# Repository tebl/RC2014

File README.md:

# RC2014

I've been spending a lot of time lately working on extensions to the excellent RC2014 machine, check out the official web page at [http://rc2014.co.uk](http://rc2014.co.uk) if you're not familiar with it. Short story; it's a Z80-based homecomputer that you can build yourself using a soldering iron, lots of time and severely burned fingers. A lot of fun indeed!

I've been documenting the build process of the various components on my blog at [https://hvetebolle.blogspot.no/p/rc2014.html](https://hvetebolle.blogspot.no/p/rc2014.html), but take note that it's in my native language of Norwegian so it might not register as readable for most people.

## Modules

I'll be making a subfolder for each of the modules I've been working on, most of the files will be in KiCad format so you'll need this open source application installed if you intend to work with the schematics. For the most part I will include the necessary Gerber files (for PCB production) in each modules export folder, the schematic in PDF-format will also probably be included - also, in the export folder.

* [RC2014 IDE ATA adapter](https://github.com/tebl/RC2014/tree/master/RC2014%20IDE)
* [RC2014 Pageable RAM](https://github.com/tebl/RC2014/tree/master/RC2014%20RAM)
* [RC2014 Tandy Sound Card](https://github.com/tebl/RC2014/tree/master/RC2014%20Tandy%20Sound%20Card)

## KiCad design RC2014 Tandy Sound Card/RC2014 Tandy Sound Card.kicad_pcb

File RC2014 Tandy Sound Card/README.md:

# RC2014 Tandy Sound Card

This is a sound card for the RC2014 that I've been tinkering with, it's based on the SN76489N chip so it should be something akin to the original Tandy Sound Card. Not that I actually had one of those mind you, I was lucky enough to have a computer in the early 90s and that was years before I managed to get a hold of my first used sound card (Creative Soundblaster 8-bit). Anyways, I digress...

# Schematic
The supplied KiCad files should be sufficient as both a schematic and as a starting point for ordering PCBs (basically you could just zip the contents of the export folder and upload that on a fabrication site), the schematic is also available in [PDF-format](https://github.com/tebl/RC2014/raw/master/RC2014%20Tandy%20Sound%20Card/export/RC2014%20Tandy%20Sound%20Card.pdf) so that you can refer to it while troubleshooting bad solder joints.

# BOM
This is the part list as it stands now, having not yet received nor assembled the first version of this card so some changes will probably happen. Note that since this includes a lot of circuitry dealing with amplifying the signal, some parts of this may be left out if they are not needed. Jack socket may be omitted if you only want to attach a simple speaker to it using the one of the two speaker outputs J2 and J3 (with amplification). Crystal may be omitted, instead you can use the system clock with the clock divider to get this below SN76489AN max frequency (4 Mhz) - with a stock RC2014 you would atleast need to set J6 to divide it in half.

| Reference | Item                                  | Count |
| --------- | ------------------------------------- | ----- |
| PCB       | Fabricate yourself using Gerber files |     1 |
| U1        | 74HCT138 DIP                          |     1 |
| U2        | 74HCT245 DIP                          |     1 |
| U3        | SN76489AN DIP                         |     1 |
| U4        | TDA7056A SIP (mono amplifier)         |     1 |
| U5        | 74HCT74 DIP                           |     1 |
| RV1 - RV2 | Adjustable resistor, 10k              |     2 |
| R1        | 1k resistor                           |     1 |
| R2, R3    | 10k resistor                          |     2 |
| X1        | TTL Oscillator, full can (DIP 14)     |     1 |
| C1-C4, C8 | 100nF ceramic capacitor               |     1 |
| C5        | 220uF electrolytic capacitor          |     1 |
| C6        | 470nF ceramic capacitor               |     1 |
| C7        | 470uF electrolytic capacitor          |     1 |
| J1        | Single row, 39p right angle connector |     1 |
| J2, J3    | Single row, 2p right angle connector  |     2 |
| J4        | Dual row, 2x08 connector              |     1 |
| J5        | FCR1295 3.5mm Jack Socket             |     1 |
| J6        | Dual row, 2x04 connector              |     1 |
| D1 - D6   | 1N4848 diode                          |     6 |

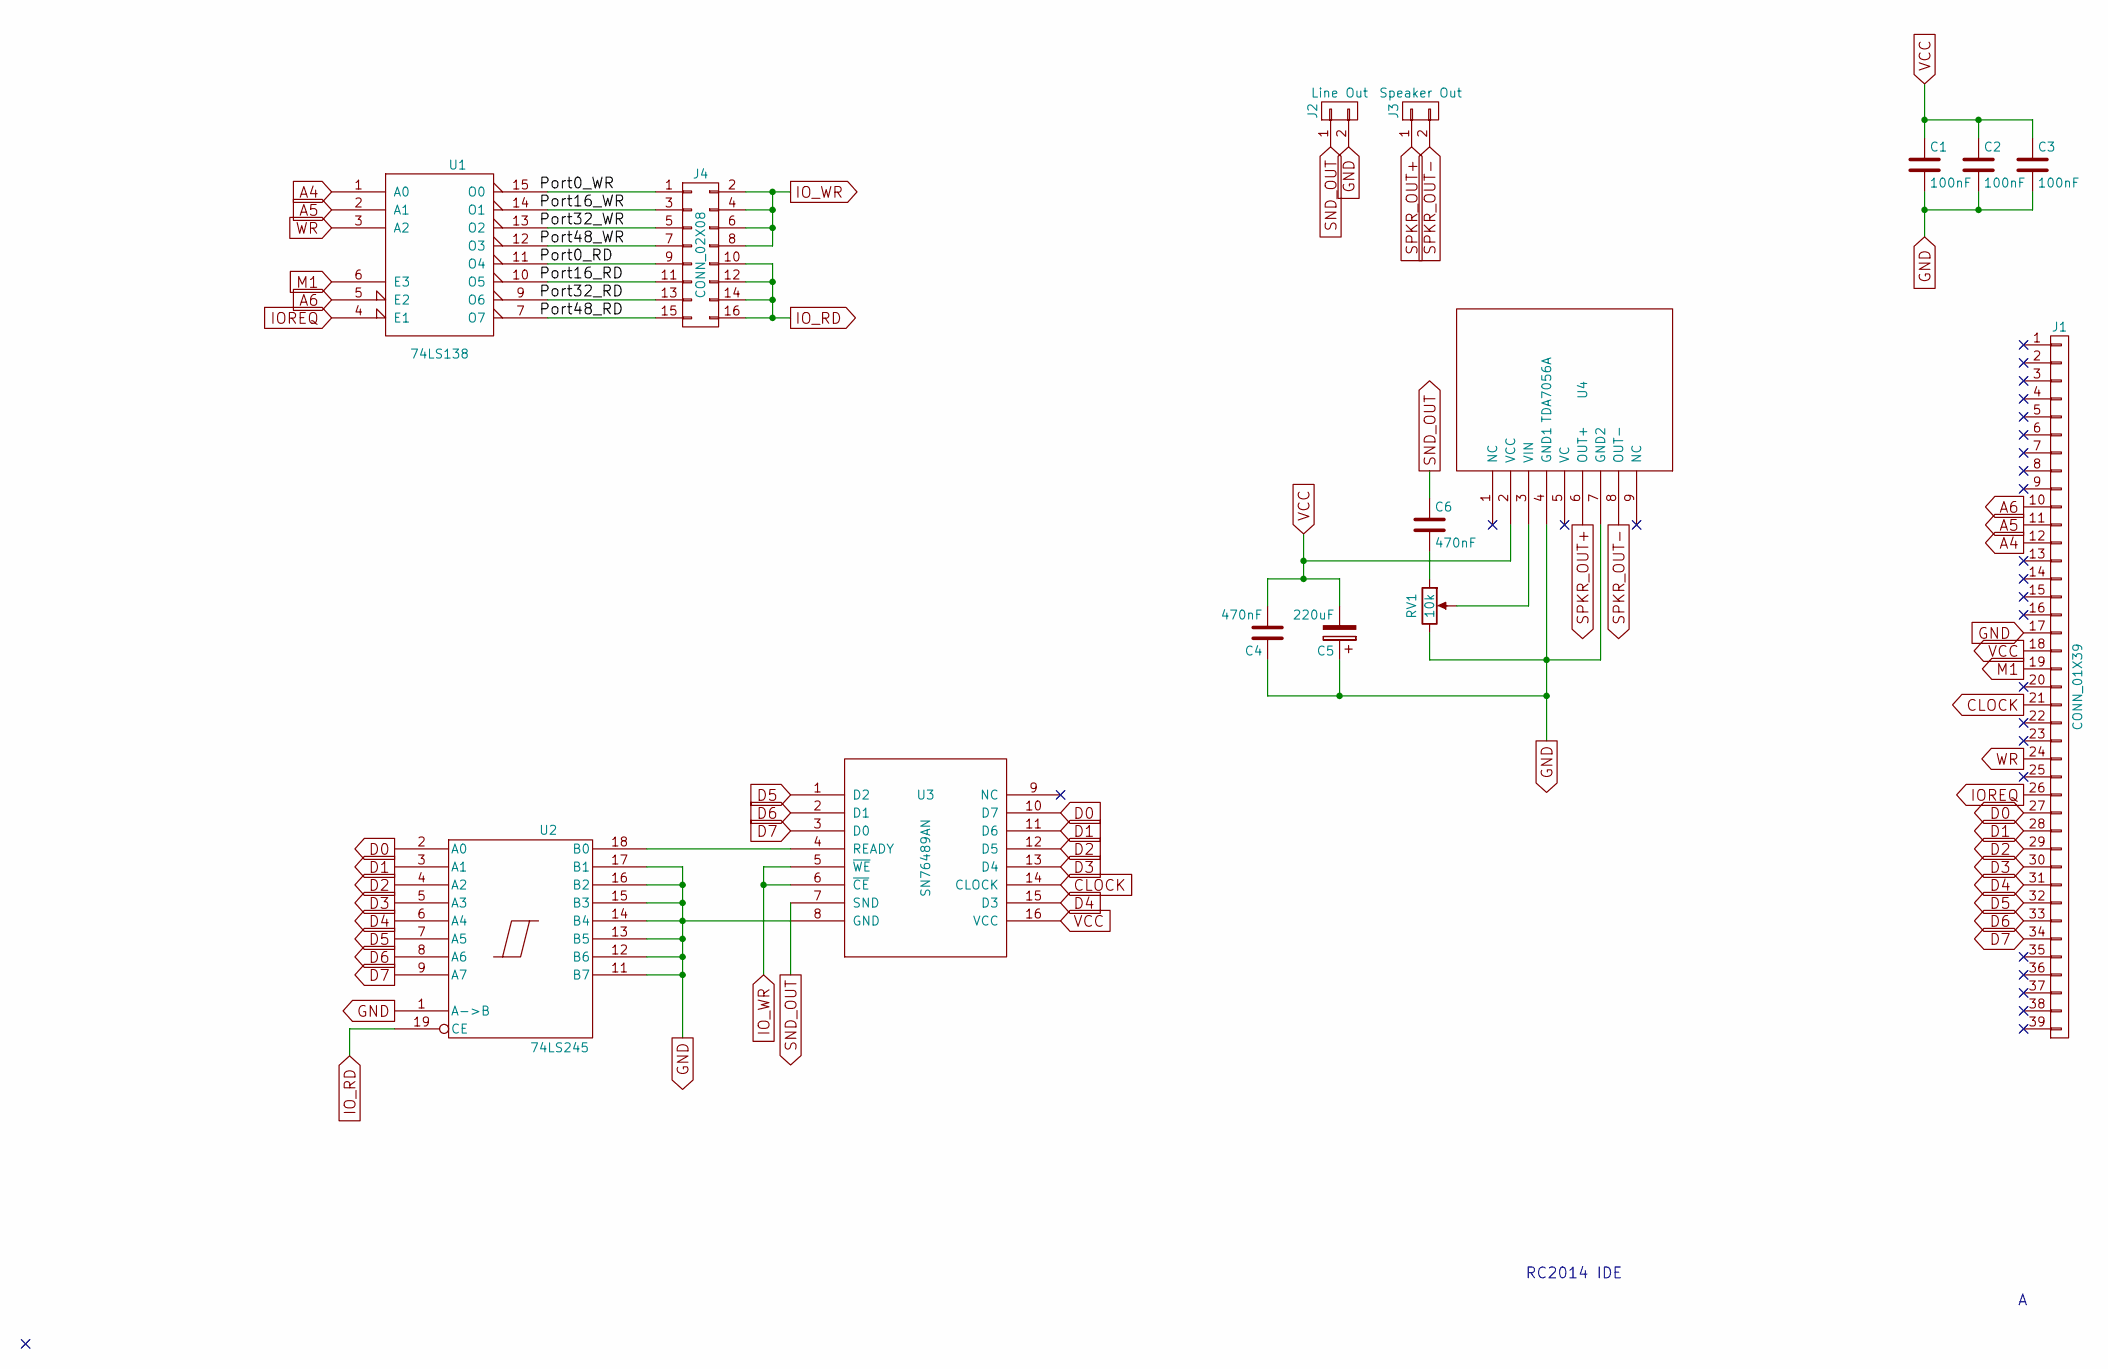
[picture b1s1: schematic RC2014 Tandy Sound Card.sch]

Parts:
C1, C2, C3: 100nF; C_Disc_D4.7mm_W2.5mm_P5.00mm
C4, C6: 470nF; C_Disc_D4.7mm_W2.5mm_P5.00mm
C5: 220uF; CP_Radial_D5.0mm_P2.00mm
J1: CONN_01X39; Pin_Header_Angled_1x39_Pitch2.54mm
J2: Line Out; Pin_Header_Angled_1x02_Pitch2.54mm
J3: Speaker Out; Pin_Header_Angled_1x02_Pitch2.54mm
J4: CONN_02X08; Pin_Header_Straight_2x08_Pitch2.54mm
RV1: 10k; Potentiometer_Trimmer_Bourns_3296W
U1: 74LS138; DIP-16_W7.62mm_Socket
U2: 74LS245; DIP-20_W7.62mm_Socket
U3: SN76489AN; DIP-16_W7.62mm_Socket
U4: TDA7056A; Pin_Header_Straight_1x09_Pitch2.54mm

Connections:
A4: J1.12, U1.1 (A0)
A5: J1.11, U1.2 (A1)
A6: J1.10, U1.5 (E2)
CLOCK: J1.21, U3.14 (CLOCK)
D0: J1.27, U2.2 (A0), U3.10 (D7)
D1: J1.28, U2.3 (A1), U3.11 (D6)
D2: J1.29, U2.4 (A2), U3.12 (D5)
D3: J1.30, U2.5 (A3), U3.13 (D4)
D4: J1.31, U2.6 (A4), U3.15 (D3)
D5: J1.32, U2.7 (A5), U3.1 (D2)
D6: J1.33, U2.8 (A6), U3.2 (D1)
D7: J1.34, U2.9 (A7), U3.3 (D0)
GND: C1.2, C2.2, C3.2, C4.1, C5.1, J1.17, J2.2, RV1.3, U1.8 (GND), U2.1 (A->B), U2.10 (GND), U2.11 (B7), U2.12 (B6), U2.13 (B5), U2.14 (B4), U2.15 (B3), U2.16 (B2), U2.17 (B1), U3.8 (GND), U4.4 (GND1), U4.7 (GND2)
IOREQ: J1.26, U1.4 (E1)
IO_RD: J4.10, J4.12, J4.14, J4.16, U2.19 (CE)
IO_WR: J4.2, J4.4, J4.6, J4.8, U3.5 (~WE), U3.6 (~CE)
M1: J1.19, U1.6 (E3)
unnamed: C6.2, RV1.1
unnamed: J4.1, U1.15 (O0)
unnamed: J4.3, U1.14 (O1)
unnamed: J4.5, U1.13 (O2)
unnamed: J4.7, U1.12 (O3)
unnamed: J4.9, U1.11 (O4)
unnamed: J4.11, U1.10 (O5)
unnamed: J4.13, U1.9 (O6)
unnamed: J4.15, U1.7 (O7)
unnamed: RV1.2, U4.3 (VIN)
unnamed: U2.18 (B0), U3.4 (READY)
SND_OUT: C6.1, J2.1, U3.7 (SND)
SPKR_OUT+: J3.1, U4.6 (OUT+)
SPKR_OUT-: J3.2, U4.8 (OUT-)
VCC: C1.1, C2.1, C3.1, C4.2, C5.2, J1.18, U1.16 (VCC), U2.20 (VCC), U3.16 (VCC), U4.2 (VCC)
WR: J1.24, U1.3 (A2)

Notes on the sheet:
RC2014 IDE

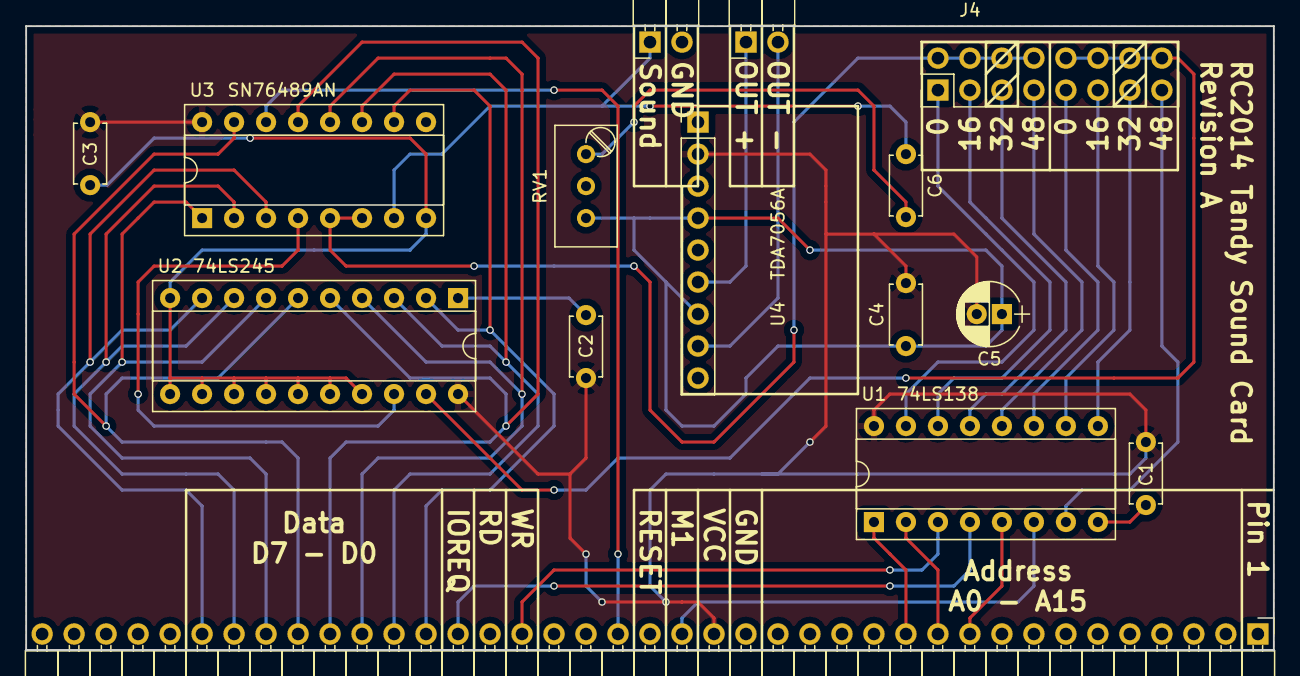
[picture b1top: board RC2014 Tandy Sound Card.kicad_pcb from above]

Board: 2 copper layers, 99.1 x 49.5 mm, 15 parts (0 on the bottom side), 33 nets.

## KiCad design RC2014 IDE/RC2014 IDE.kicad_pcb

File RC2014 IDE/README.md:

# RC2014 IDE ATA adapter

This is an IDE ATA adapter I've been working so that I can avoid having to learn how to solder surface mount components like the one used on the officialy available Compact Flash module. This gives you a standard ATA IDE connector that you can use for anything that still supports 8-bit IDE, where this relates to the Compact Flash module is that you can use it to connect up to a cheap Compact Flash to IDE adapter. See Scripts for a sample Basic-script that can be used to test the adapter.

# Schematic
The supplied KiCad files should be sufficient as both a schematic and as a starting point for ordering PCBs (basically you could just zip the contents of the export folder and upload that on a fabrication site), the schematic is also available in [PDF-format](https://github.com/tebl/RC2014/raw/master/RC2014%20IDE/export/RC2014%20IDE.pdf) so that you can refer to it while troubleshooting bad solder joints.

# BOM
| Reference | Item                                  | Count |
| --------- | ------------------------------------- | ----- |
| PCB       | Fabricate yourself using Gerber files |     1 |
| R1 - R3   | 1k resistor                           |     3 |
| R4        | 330 resistor                          |     1 |
| J1        | Dual row, 20p right angle connector   |     1 |
| J2        | Single row, 4p right angle connector  |     1 |
| J4        | Single row, 39p right angle connector |     1 |
| C1        | Ceramic capacitor, disc 100nF         |     1 |
|           | 40 pin IDE cable (gray type)          |     1 |
|           | CF to IDE ATA adapter                 |     1 |

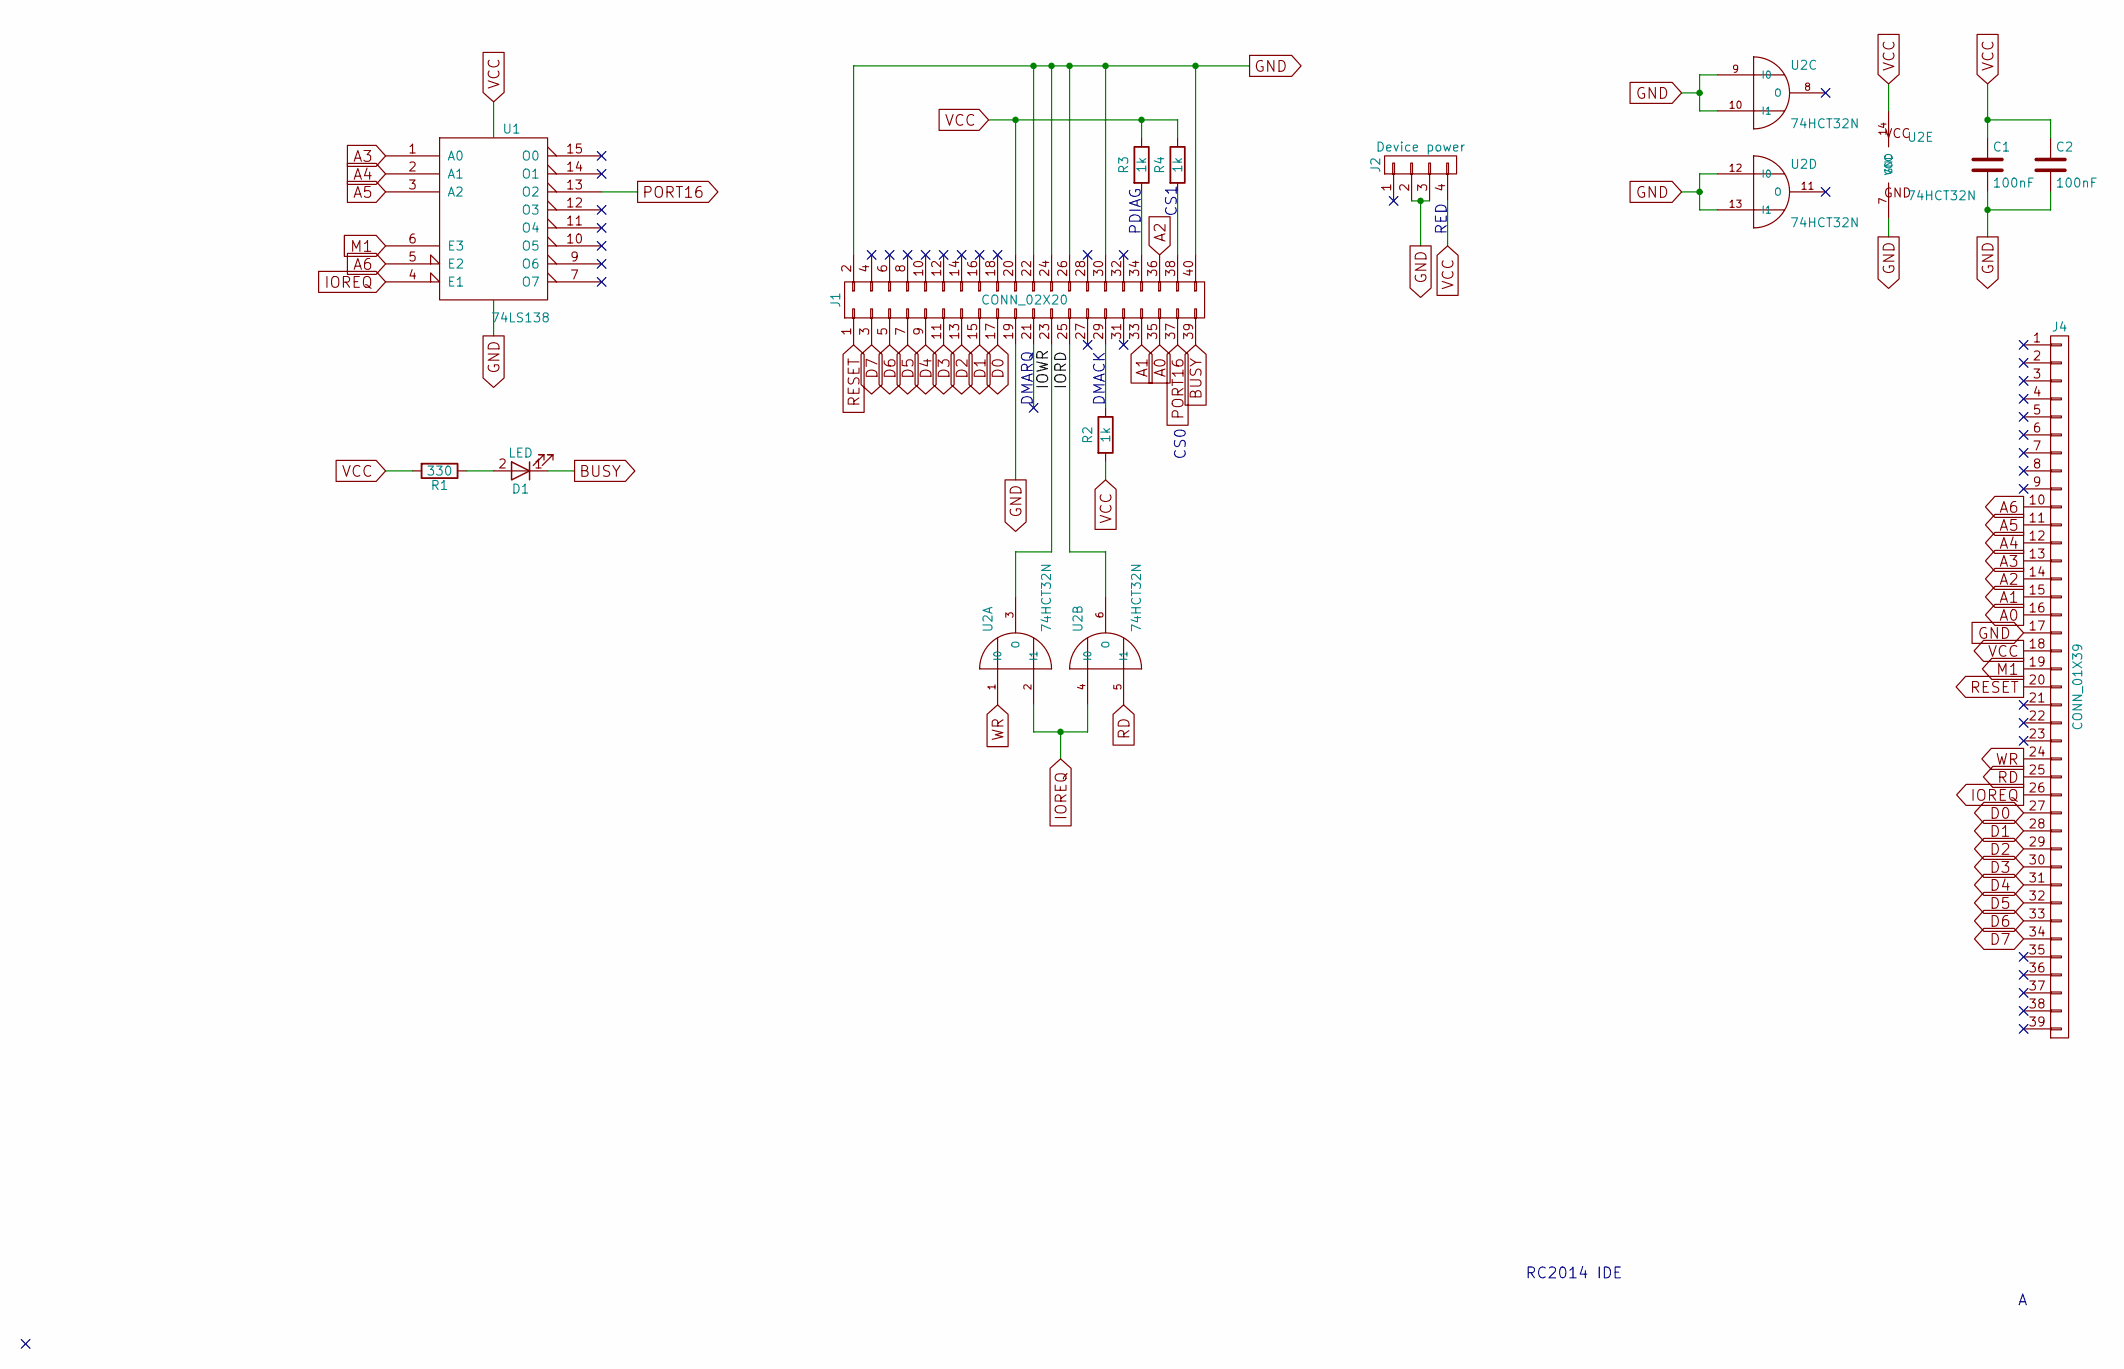
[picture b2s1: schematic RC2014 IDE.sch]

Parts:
C1, C2: 100nF; C_Disc_D4.7mm_W2.5mm_P5.00mm
D1: LED; LED_D3.0mm
J1: CONN_02X20; IDC_Header_Straight_40pins
J2: Device power; Pin_Header_Angled_1x04_Pitch2.54mm
J4: CONN_01X39; Pin_Header_Angled_1x39_Pitch2.54mm
R1: 330; R_Axial_DIN0207_L6.3mm_D2.5mm_P10.16mm_Horizontal
R2, R3, R4: 1k; R_Axial_DIN0207_L6.3mm_D2.5mm_P10.16mm_Horizontal
U1: 74LS138; DIP-16_W7.62mm_Socket
U2: 74HCT32N; DIP-14_W7.62mm_Socket

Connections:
/IORD: J1.25, U2.6 (O)
/IOWR: J1.23, U2.3 (O)
A0: J1.35, J4.16
A1: J1.33, J4.15
A2: J1.36, J4.14
A3: J4.13, U1.1 (A0)
A4: J4.12, U1.2 (A1)
A5: J4.11, U1.3 (A2)
A6: J4.10, U1.5 (E2)
BUSY: D1.1 (K), J1.39
D0: J1.17, J4.27
D1: J1.15, J4.28
D2: J1.13, J4.29
D3: J1.11, J4.30
D4: J1.9, J4.31
D5: J1.7, J4.32
D6: J1.5, J4.33
D7: J1.3, J4.34
GND: C1.2, C2.2, J1.2, J1.19, J1.22, J1.24, J1.26, J1.30, J1.40, J2.2, J2.3, J4.17, U1.8 (GND), U2.7 (GND), U2.9 (I0), U2.10 (I1), U2.12 (I0), U2.13 (I1)
IOREQ: J4.26, U1.4 (E1), U2.2 (I1), U2.4 (I0)
M1: J4.19, U1.6 (E3)
unnamed: D1.2 (A), R1.1
unnamed: J1.29, R2.1
unnamed: J1.34, R3.2
unnamed: J1.38, R4.2
PORT16: J1.37, U1.13 (O2)
RD: J4.25, U2.5 (I1)
RESET: J1.1, J4.20
VCC: C1.1, C2.1, J1.20, J2.4, J4.18, R1.2, R2.2, R3.1, R4.1, U1.16 (VCC), U2.14 (VCC)
WR: J4.24, U2.1 (I0)

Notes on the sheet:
RC2014 IDE
CS1
CS0
PDIAG
DMACK
RED
DMARQ

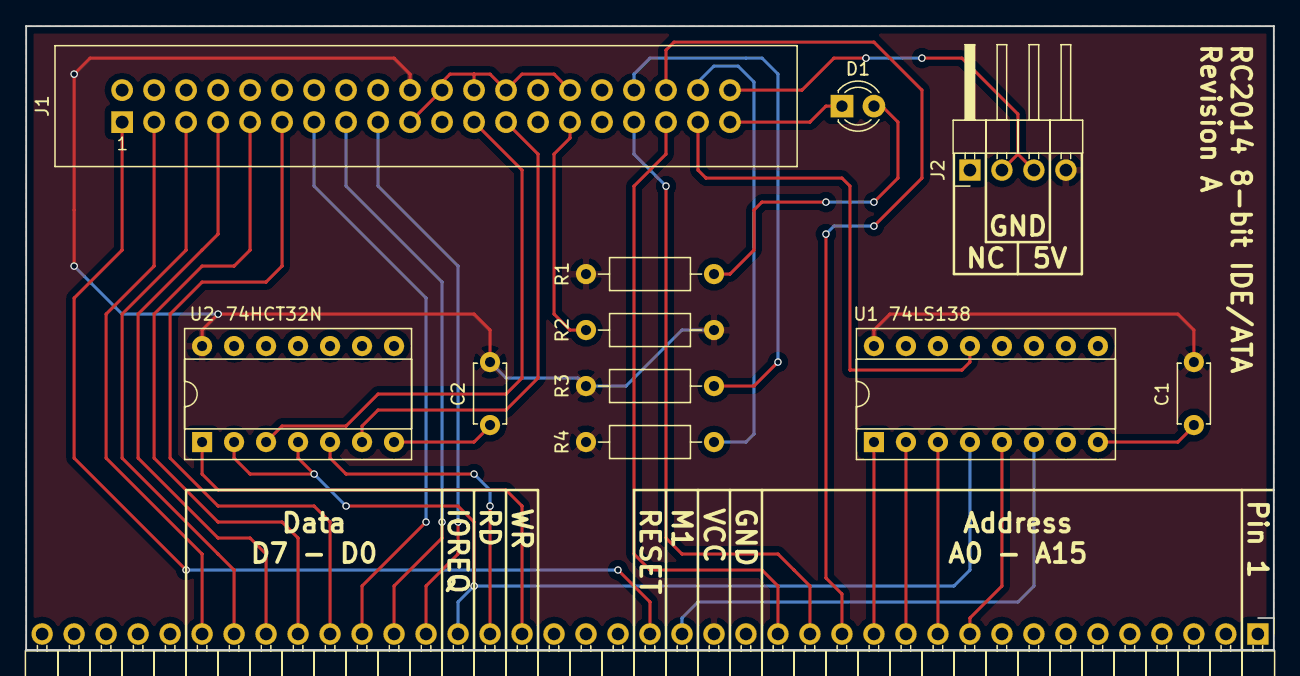
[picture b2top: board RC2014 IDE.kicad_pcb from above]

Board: 2 copper layers, 99.1 x 49.5 mm, 12 parts (0 on the bottom side), 30 nets.

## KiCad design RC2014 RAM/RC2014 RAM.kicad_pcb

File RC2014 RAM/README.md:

# RC2014 RAM

This is a customized RAM module that enables you to page the module in and out, similar to the 64K module available. The difference here is that I'm only using one RAM chip per card. The reason for this is simple, PCB manufacturers don't seem to want to make a single PCB so this way I can use more of them at once!

The PCB places the paging pin on one of the spare pins of the backplane, that way I don't have to run any wires between the cards.

# Schematic
The supplied KiCad files should be sufficient as both a schematic and as a starting point for ordering PCBs (basically you could just zip the contents of the export folder and upload that on a fabrication site), the schematic is also available in [PDF-format](https://github.com/tebl/RC2014/raw/master/RC2014%20RAM/export/RC2014%20RAM.pdf) so that you can refer to it while troubleshooting bad solder joints.

# BOM
| Reference | Item                                  | Count |
| --------- | ------------------------------------- | ----- |
| PCB       | Fabricate yourself using Gerber files |     1 |
| U1        | 62256 32k * bit Static RAM            |     1 |
| U2        | 74HCT32 DIP                           |     1 |
| U3        | 74HCT00 DIP                           |     1 |
| J2        | Single row, 3p right angle connector  |     1 |
| J1, J3    | Single row, 2p right angle connector  |     2 |
| J4        | Single row, 39p right angle connector |     1 |
| C1 - C3   | Ceramic capacitor, disc 100nF         |     3 |

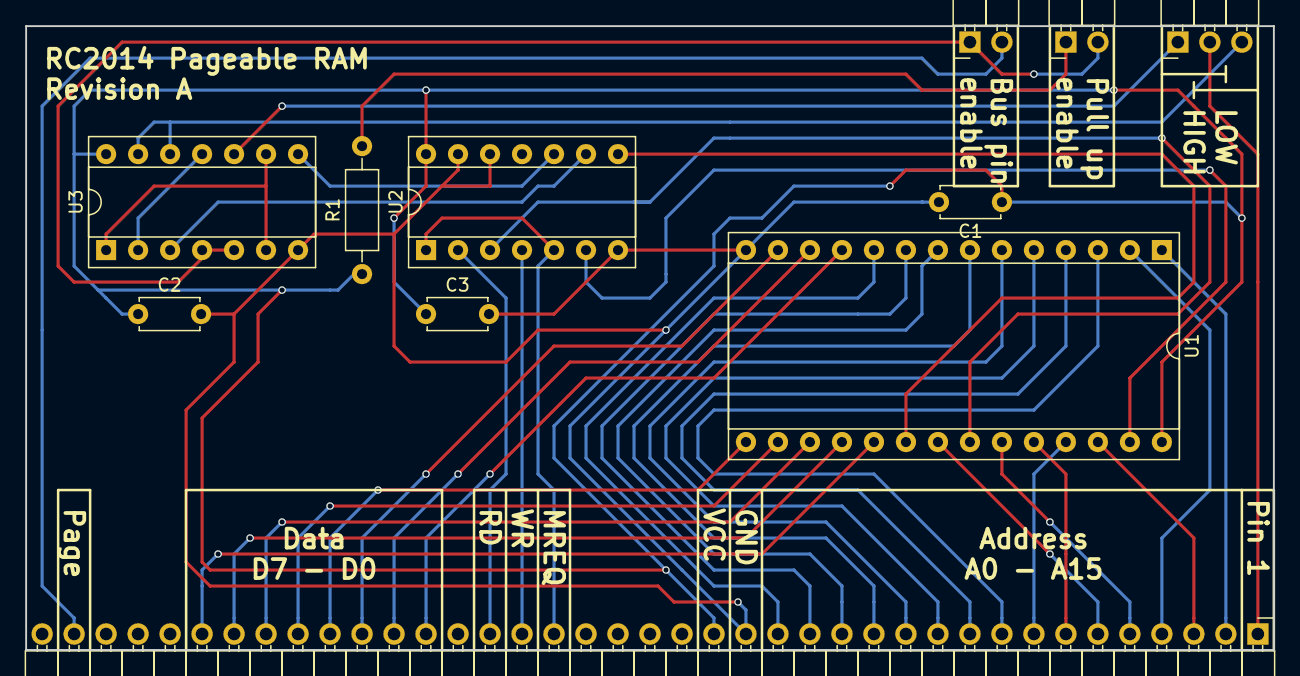
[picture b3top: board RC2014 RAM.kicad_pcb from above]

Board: 2 copper layers, 99.1 x 49.5 mm, 11 parts (0 on the bottom side), 41 nets.

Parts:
C1, C2, C3: 100nF; C_Disc_D4.7mm_W2.5mm_P5.00mm
J1: Page PullUp; Pin_Header_Angled_1x02_Pitch2.54mm
J2: HIGH | LOW; Pin_Header_Angled_1x03_Pitch2.54mm
J3: Bus enable; Pin_Header_Angled_1x02_Pitch2.54mm
J4: CONN_01X39; Pin_Header_Angled_1x39_Pitch2.54mm
R1: 10k; R_Axial_DIN0207_L6.3mm_D2.5mm_P10.16mm_Horizontal
U1: HM62256BLP-7; DIP-28_W15.24mm_Socket
U2: 74LS32; DIP-14_W7.62mm_Socket
U3: 74HCT00; DIP-14_W7.62mm_Socket

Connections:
A0: J4.16, U1.10
A1: J4.15, U1.9
A2: J4.14, U1.8
A3: J4.13, U1.7
A4: J4.12, U1.6
A5: J4.11, U1.5
A6: J4.10, U1.4
A7: J4.9, U1.3
A8: J4.8, U1.25
A9: J4.7, U1.24
A10: J4.6, U1.21
A11: J4.5, U1.23
A12: J4.4, U1.2
A13: J4.3, U1.26
A14: J4.2, U1.1
A15: J2.2, J4.1
CS: U1.20, U2.8
D0: J4.27, U1.11
D1: J4.28, U1.12
D2: J4.29, U1.13
D3: J4.30, U1.15
D4: J4.31, U1.16
D5: J4.32, U1.17
D6: J4.33, U1.18
D7: J4.34, U1.19
EN: U3.1, U3.6, U3.9
GND: C1.2, C2.2, C3.2, J4.17, U1.14, U2.7, U2.12, U2.13, U3.7
HIGH: J2.1, U3.10
LOW: J2.3, U3.12, U3.13
MREQ: J4.23, U2.1, U2.5
unnamed: J1.1, R1.2
unnamed: J3.2, J4.38
unnamed: U1.22, U2.3
unnamed: U1.27, U2.6
unnamed: U2.9, U3.3
unnamed: U2.10, U3.8
unnamed: U3.2, U3.11
PAGE: J1.2, J3.1, U3.4, U3.5
RD: J4.25, U2.2
VCC: C1.1, C2.1, C3.1, J4.18, R1.1, U1.28, U2.14, U3.14
WR: J4.24, U2.4

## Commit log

2017-05-13 Added IDE Compact Flash Card
2017-05-13 Chose wrong license
2017-05-13 Added basic script for reading Compact Flash card.
2017-05-13 Moved gallery files
2017-05-13 Added custom pageable RAM module
2017-05-13 Fixed typo
2017-05-13 Added RAM pcb
2017-05-13 Fixed url-
2017-05-13 Let's try that again!
2017-05-13 Added IDE readme with BOM
2017-05-13 Fix table
2017-05-13 Added readme schematic note
2017-05-13 Added completed image
2017-05-13 Added RC2014 Tandy Sound Card
2017-05-13 Added TDA7065A audio amplification
2017-05-14 Added OR-gates to R/W signals
    Seems other people have been having problems when using RD and WR directly, so adding the OR-gates just in case I need them and can't afford to remake the PCBs.
2017-05-15 Renumbered ICs to be consistent
2017-05-15 Exported files
2017-05-15 Added pinheaders for selecting address
2017-05-19 Reorganized images and added images for revised version of iDE adapter.
2017-05-19 Updated readme to match where I moved IDE pictures.
2017-05-19 Moved some images
2017-05-19 Added RC2014 Tandy Sound Card pcb preview and plotted the schematic.
2017-05-19 Files missing from previous commit.
2017-06-11 Added volume control
2017-06-13 Tandy Sound card revision A
    PCB layout done including silkscreen. Includes TDA7056A mono amplifier circuit.
2017-06-13 Updated README.
2017-06-13 Fixed RAM README pcb url.
2017-06-13 Added Tandy Sound Card BOM.
2017-06-15 Tandy sound card exports.
